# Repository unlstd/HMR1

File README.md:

> This repo documents my progress in creating my first fully functional 16-bit computer. At first, it wasn't even supposed to be public. I made it public mainly to make it easier to work on the project across different devices and to get quicker help from my friends. Because of that, please consider this project more as a documentation of someone's progress rather than a fully documented architecture.

With that being said, I can now introduce you to the project and what I'm trying to achieve.

HMR1 is a 16-bit, non-pipelined computer running at 4 MHz with 8 GPRs.

It contains the following components:

* ALU with two 16-bit special registers for latching operands
* MAR
* MDR
* SP
* HP
* IR
* 8 × 16-bit GPRs
* FR
* PC (also known as IP)
* Internal 4 MHz clock and reset signal generator
* CU
* IC (Interrupt Controller)

The computer itself is still a work in progress, but most of it is already done.

You can track the progress using the checklist below:

* [x] ALU
* [x] MAR
* [x] MDR
* [x] SP
* [x] HP
* [x] GPRs
* [x] FR
* [x] PC
* [x] IR
* [x] IC
* [x] CU
* [x] Motherboard
* [x] Internal 4 MHz clock and reset signal generator

So, even though all the schematics are complete, that doesn't mean the PCBs have been made yet. Here's a little checklist to track the progress of designing the actual PCBs:

* [ ] ALU
* [ ] MAR
* [x] MDR
* [x] SP
* [x] HP
* [x] GPRs
* [ ] FR
* [x] PC
* [ ] IR
* [ ] IC
* [ ] CU
* [ ] Motherboard
* [ ] Internal 4 MHz clock and reset signal generator

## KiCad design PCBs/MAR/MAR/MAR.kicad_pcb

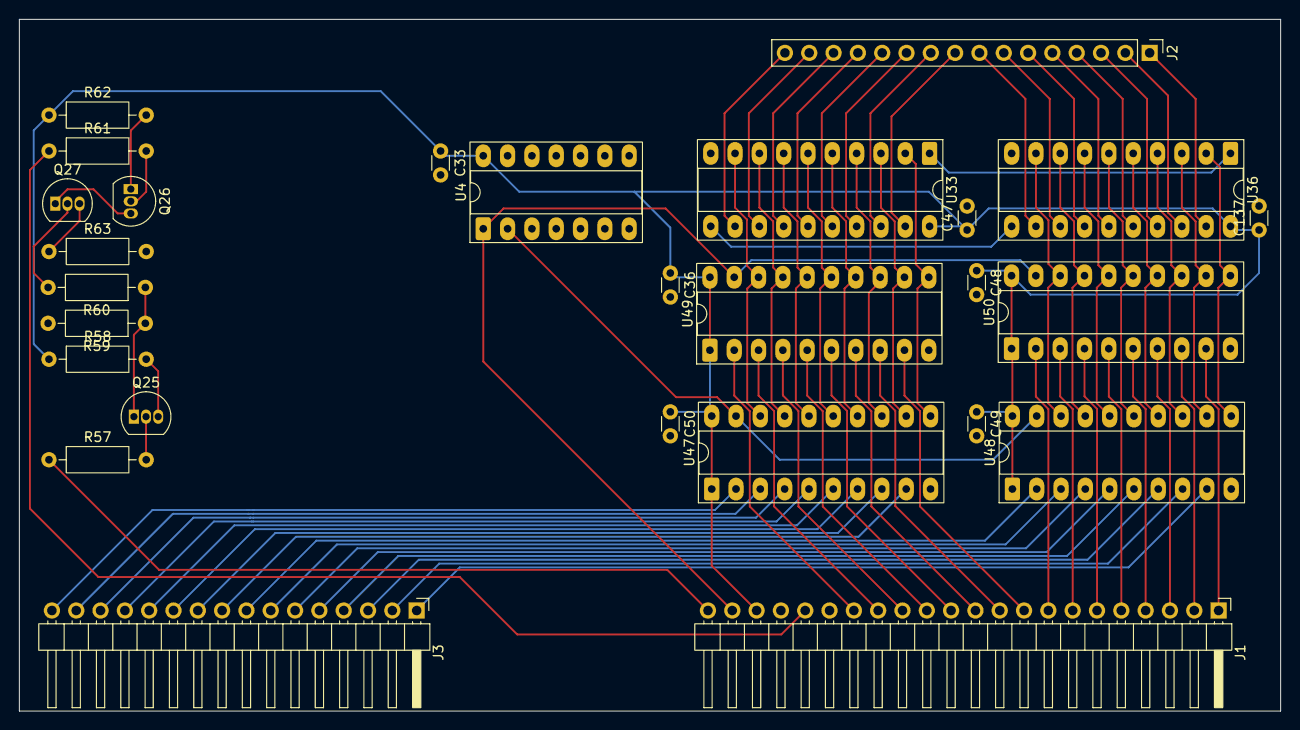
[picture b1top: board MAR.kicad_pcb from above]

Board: 2 copper layers, 131.8 x 72.2 mm, 27 parts (0 on the bottom side), 80 nets.

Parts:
C33, C36, C47, C48, C49, C50, C137: 100nF; C_Disc_D3.0mm_W1.6mm_P2.50mm
J1: MAR_DATA; PinHeader_1x22_P2.54mm_Horizontal
J2: MAR_MC; PinHeader_1x16_P2.54mm_Vertical
J3: MAR_ADDR; PinHeader_1x16_P2.54mm_Horizontal
Q25: BC557; TO-92_Inline
Q26, Q27: BC547; TO-92_Inline
R57, R58, R59, R60, R61, R62, R63: 10k; R_Axial_DIN0207_L6.3mm_D2.5mm_P10.16mm_Horizontal
U4: 74HC04; DIP-14_W7.62mm_Socket_LongPads
U33, U36: 74HC574_w_Pwr; DIP-20_W7.62mm_Socket_LongPads
U47, U48, U49, U50: 74HC245; DIP-20_W7.62mm_Socket_LongPads

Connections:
/A0: J3.1, U48.9 (A7)
/A1: J3.2, U48.8 (A6)
/A2: J3.3, U48.7 (A5)
/A3: J3.4, U48.6 (A4)
/A4: J3.5, U48.5 (A3)
/A5: J3.6, U48.4 (A2)
/A6: J3.7, U48.3 (A1)
/A7: J3.8, U48.2 (A0)
/A8: J3.9, U47.9 (A7)
/A9: J3.10, U47.8 (A6)
/A10: J3.11, U47.7 (A5)
/A11: J3.12, U47.6 (A4)
/A12: J3.13, U47.5 (A3)
/A13: J3.14, U47.4 (A2)
/A14: J3.15, U47.3 (A1)
/A15: J3.16, U47.2 (A0)
/CLK: J1.18, R61.1
/D0: J1.1, U50.9 (A7)
/D1: J1.2, U50.8 (A6)
/D2: J1.3, U50.7 (A5)
/D3: J1.4, U50.6 (A4)
/D4: J1.5, U50.5 (A3)
/D5: J1.6, U50.4 (A2)
/D6: J1.7, U50.3 (A1)
/D7: J1.8, U50.2 (A0)
/D8: J1.9, U49.9 (A7)
/D9: J1.10, U49.8 (A6)
/D10: J1.11, U49.7 (A5)
/D11: J1.12, U49.6 (A4)
/D12: J1.13, U49.5 (A3)
/D13: J1.14, U49.4 (A2)
/D14: J1.15, U49.3 (A1)
/D15: J1.16, U49.2 (A0)
/M0: J2.1, U36.19 (Q0)
/M1: J2.2, U36.18 (Q1)
/M2: J2.3, U36.17 (Q2)
/M3: J2.4, U36.16 (Q3)
/M4: J2.5, U36.15 (Q4)
/M5: J2.6, U36.14 (Q5)
/M6: J2.7, U36.13 (Q6)
/M7: J2.8, U36.12 (Q7)
/M8: J2.9, U33.19 (Q0)
/M9: J2.10, U33.18 (Q1)
/M10: J2.11, U33.17 (Q2)
/M11: J2.12, U33.16 (Q3)
/M12: J2.13, U33.15 (Q4)
/M13: J2.14, U33.14 (Q5)
/M14: J2.15, U33.13 (Q6)
/M15: J2.16, U33.12 (Q7)
/MAR_GATE[0->DATA;1->ADDR]: J1.21, U4.1, U49.19 (CE), U50.19 (CE)
/MAR_IN#: J1.22, R57.1
/Vcc: C33.1, C36.1, C47.1, C48.1, C49.1, C50.1, C137.1, J1.20, R58.1, R62.1, U4.14 (VCC), U33.20 (Vcc), U36.20 (Vcc), U47.1 (A->B), U47.20 (VCC), U48.1 (A->B), U48.20 (VCC), U49.1 (A->B), U49.20 (VCC), U50.1 (A->B), U50.20 (VCC)
GND: C33.2, C36.2, C47.2, C48.2, C49.2, C50.2, C137.2, J1.19, R59.2, R63.2, U4.7 (GND), U33.10 (GND), U36.10 (GND), U47.10 (GND), U48.10 (GND), U49.10 (GND), U50.10 (GND)
unnamed: U33.11 (CP), U36.11 (CP)
unnamed: Q27.3 (E), R63.1
unnamed: U33.1 (~OE), U36.1 (~OE)
unnamed: Q25.2 (B), R57.2
unnamed: Q25.1 (C), R59.1, R60.1
unnamed: Q25.3 (E), R58.2
unnamed: Q26.2 (B), R61.2
unnamed: Q26.1 (C), R62.2
unnamed: Q26.3 (E), Q27.1 (C)
unnamed: Q27.2 (B), R60.2
unnamed: U33.2 (D0), U47.11 (B7), U49.11 (B7)
unnamed: U33.3 (D1), U47.12 (B6), U49.12 (B6)
unnamed: U33.4 (D2), U47.13 (B5), U49.13 (B5)
unnamed: U33.5 (D3), U47.14 (B4), U49.14 (B4)
unnamed: U33.6 (D4), U47.15 (B3), U49.15 (B3)
unnamed: U33.7 (D5), U47.16 (B2), U49.16 (B2)
unnamed: U33.8 (D6), U47.17 (B1), U49.17 (B1)
unnamed: U33.9 (D7), U47.18 (B0), U49.18 (B0)
unnamed: U36.2 (D0), U48.11 (B7), U50.11 (B7)
unnamed: U36.3 (D1), U48.12 (B6), U50.12 (B6)
unnamed: U36.4 (D2), U48.13 (B5), U50.13 (B5)
unnamed: U36.5 (D3), U48.14 (B4), U50.14 (B4)
unnamed: U36.6 (D4), U48.15 (B3), U50.15 (B3)
unnamed: U36.7 (D5), U48.16 (B2), U50.16 (B2)
unnamed: U36.8 (D6), U48.17 (B1), U50.17 (B1)
unnamed: U36.9 (D7), U48.18 (B0), U50.18 (B0)
unnamed: U4.2, U47.19 (CE), U48.19 (CE)

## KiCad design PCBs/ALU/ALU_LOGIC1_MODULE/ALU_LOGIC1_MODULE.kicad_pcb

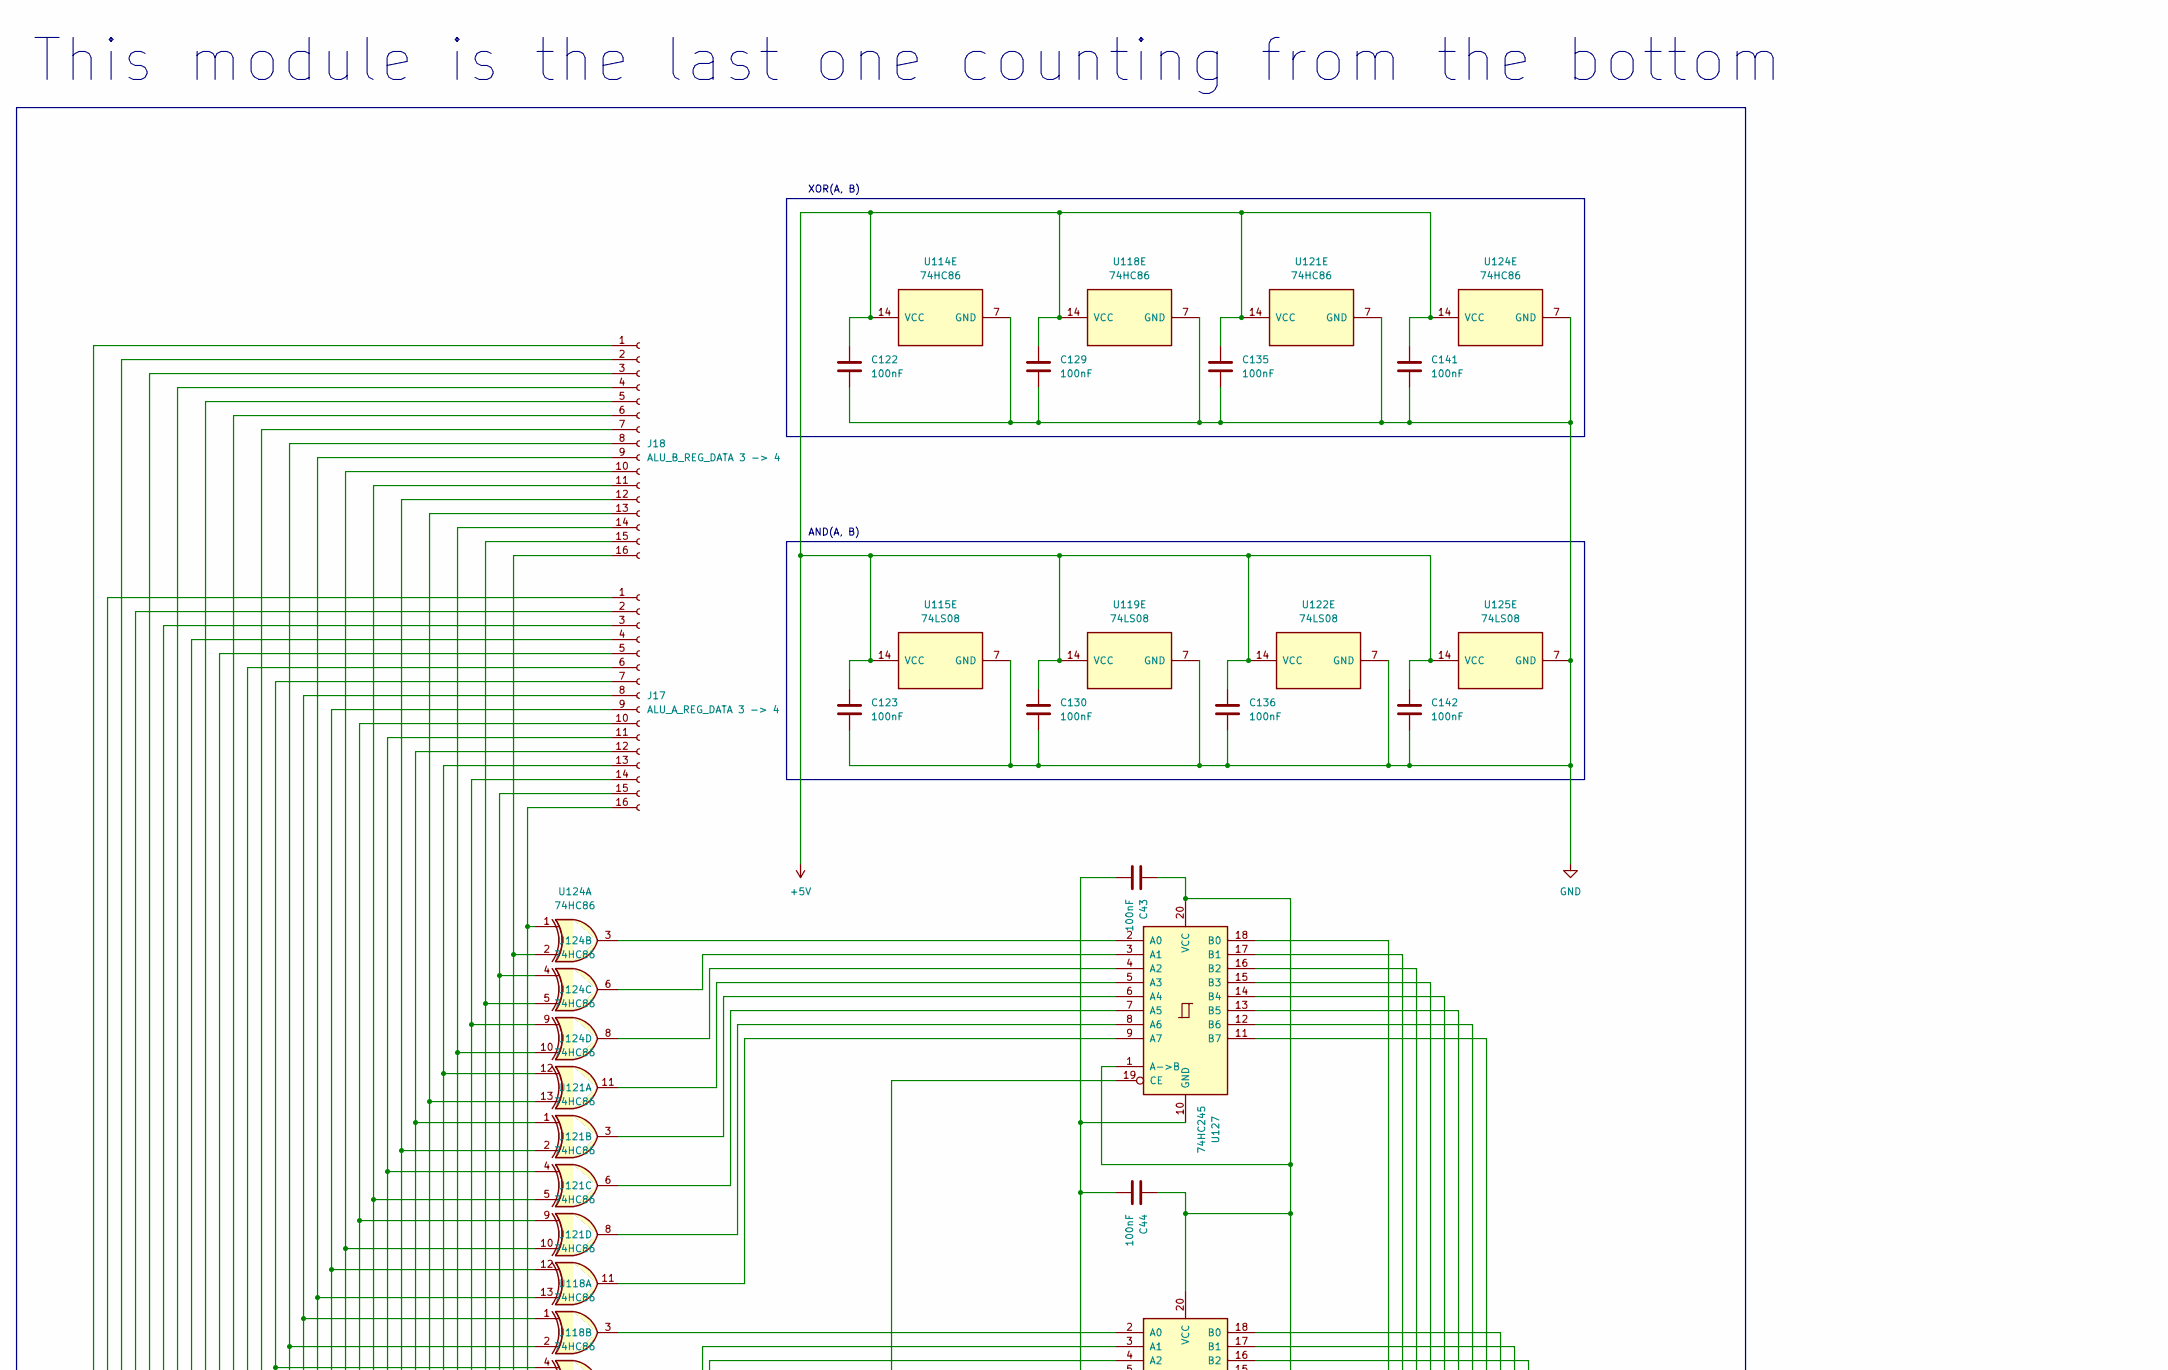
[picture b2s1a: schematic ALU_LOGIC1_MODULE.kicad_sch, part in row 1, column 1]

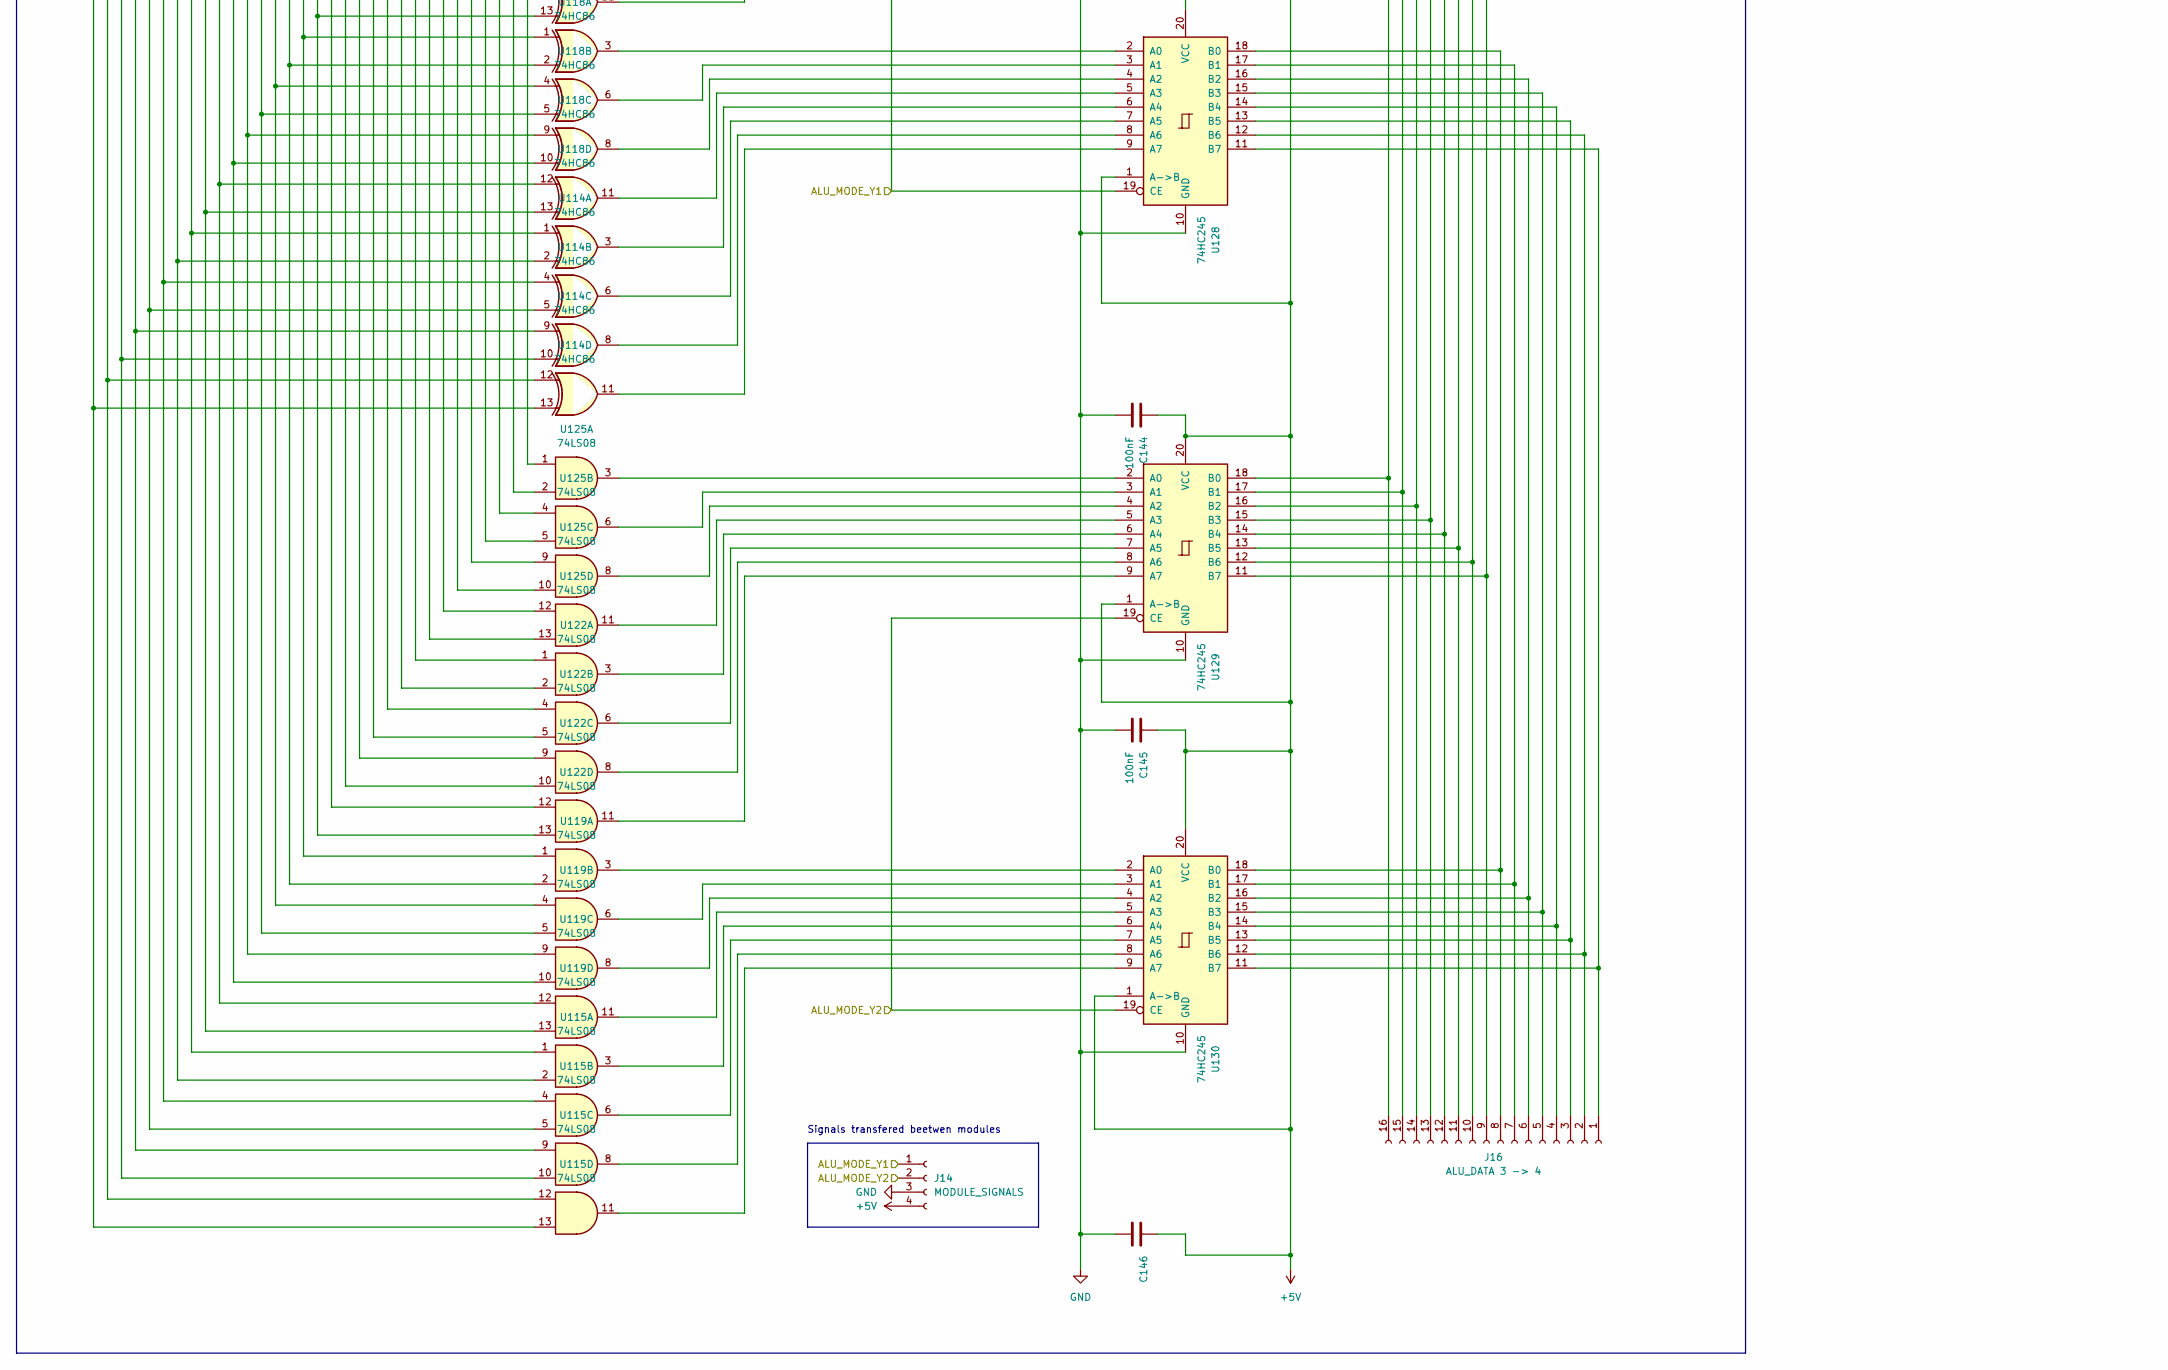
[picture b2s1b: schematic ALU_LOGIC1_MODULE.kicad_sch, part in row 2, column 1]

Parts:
C43, C44, C122, C123, C129, C130, C135, C136, C141, C142, C144, C145, C146: 100nF; C_Disc_D3.0mm_W1.6mm_P2.50mm
J14: MODULE_SIGNALS; PinSocket_1x04_P2.54mm_Vertical
J16: ALU_DATA 3 -> 4; PinSocket_1x16_P2.54mm_Vertical
J17: ALU_A_REG_DATA 3 -> 4; PinSocket_1x16_P2.54mm_Vertical
J18: ALU_B_REG_DATA 3 -> 4; PinSocket_1x16_P2.54mm_Vertical
U114, U118, U121, U124: 74HC86; DIP-14_W7.62mm_Socket_LongPads
U115, U119, U122, U125: 74LS08; DIP-14_W7.62mm_Socket_LongPads
U127, U128, U129, U130: 74HC245; DIP-20_W7.62mm_Socket_LongPads

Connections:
+5V: C43.1, C44.1, C122.1, C123.1, C129.1, C130.1, C135.1, C136.1, C141.1, C142.1, C144.1, C145.1, C146.1, J14.4, U114.14 (VCC), U115.14 (VCC), U118.14 (VCC), U119.14 (VCC), U121.14 (VCC), U122.14 (VCC), U124.14 (VCC), U125.14 (VCC), U127.1 (A->B), U127.20 (VCC), U128.1 (A->B), U128.20 (VCC), U129.1 (A->B), U129.20 (VCC), U130.1 (A->B), U130.20 (VCC)
/ALU_MODE_Y1: J14.1, U127.19 (CE), U128.19 (CE)
/ALU_MODE_Y2: J14.2, U129.19 (CE), U130.19 (CE)
GND: C43.2, C44.2, C122.2, C123.2, C129.2, C130.2, C135.2, C136.2, C141.2, C142.2, C144.2, C145.2, C146.2, J14.3, U114.7 (GND), U115.7 (GND), U118.7 (GND), U119.7 (GND), U121.7 (GND), U122.7 (GND), U124.7 (GND), U125.7 (GND), U127.10 (GND), U128.10 (GND), U129.10 (GND), U130.10 (GND)
unnamed: J16.1, U128.11 (B7), U130.11 (B7)
unnamed: J16.2, U128.12 (B6), U130.12 (B6)
unnamed: J16.3, U128.13 (B5), U130.13 (B5)
unnamed: J16.4, U128.14 (B4), U130.14 (B4)
unnamed: J16.5, U128.15 (B3), U130.15 (B3)
unnamed: J16.6, U128.16 (B2), U130.16 (B2)
unnamed: J16.7, U128.17 (B1), U130.17 (B1)
unnamed: J16.8, U128.18 (B0), U130.18 (B0)
unnamed: J16.9, U127.11 (B7), U129.11 (B7)
unnamed: J16.10, U127.12 (B6), U129.12 (B6)
unnamed: J16.11, U127.13 (B5), U129.13 (B5)
unnamed: J16.12, U127.14 (B4), U129.14 (B4)
unnamed: J16.13, U127.15 (B3), U129.15 (B3)
unnamed: J16.14, U127.16 (B2), U129.16 (B2)
unnamed: J16.15, U127.17 (B1), U129.17 (B1)
unnamed: J16.16, U127.18 (B0), U129.18 (B0)
unnamed: J17.1, U114.12, U115.12
unnamed: J17.2, U114.9, U115.9
unnamed: J17.3, U114.4, U115.4
unnamed: J17.4, U114.1, U115.1
unnamed: J17.5, U118.12, U119.12
unnamed: J17.6, U118.9, U119.9
unnamed: J17.7, U118.4, U119.4
unnamed: J17.8, U118.1, U119.1
unnamed: J17.9, U121.12, U122.12
unnamed: J17.10, U121.9, U122.9
unnamed: J17.11, U121.4, U122.4
unnamed: J17.12, U121.1, U122.1
unnamed: J17.13, U124.12, U125.12
unnamed: J17.14, U124.9, U125.9
unnamed: J17.15, U124.4, U125.4
unnamed: J17.16, U124.1, U125.1
unnamed: J18.1, U114.13, U115.13
unnamed: J18.2, U114.10, U115.10
unnamed: J18.3, U114.5, U115.5
unnamed: J18.4, U114.2, U115.2
unnamed: J18.5, U118.13, U119.13
unnamed: J18.6, U118.10, U119.10
unnamed: J18.7, U118.5, U119.5
unnamed: J18.8, U118.2, U119.2
unnamed: J18.9, U121.13, U122.13
unnamed: J18.10, U121.10, U122.10
unnamed: J18.11, U121.5, U122.5
unnamed: J18.12, U121.2, U122.2
unnamed: J18.13, U124.13, U125.13
unnamed: J18.14, U124.10, U125.10
unnamed: J18.15, U124.5, U125.5
unnamed: J18.16, U124.2, U125.2
unnamed: U124.3, U127.2 (A0)
unnamed: U124.6, U127.3 (A1)
unnamed: U124.8, U127.4 (A2)
unnamed: U124.11, U127.5 (A3)
unnamed: U121.3, U127.6 (A4)
unnamed: U121.6, U127.7 (A5)
unnamed: U121.8, U127.8 (A6)
unnamed: U121.11, U127.9 (A7)
unnamed: U118.3, U128.2 (A0)
unnamed: U118.6, U128.3 (A1)
unnamed: U118.8, U128.4 (A2)
unnamed: U118.11, U128.5 (A3)
unnamed: U114.3, U128.6 (A4)
unnamed: U114.6, U128.7 (A5)
unnamed: U114.8, U128.8 (A6)
unnamed: U114.11, U128.9 (A7)
unnamed: U125.3, U129.2 (A0)
unnamed: U125.6, U129.3 (A1)
unnamed: U125.8, U129.4 (A2)
unnamed: U125.11, U129.5 (A3)
unnamed: U122.3, U129.6 (A4)
unnamed: U122.6, U129.7 (A5)
unnamed: U122.8, U129.8 (A6)
unnamed: U122.11, U129.9 (A7)
unnamed: U119.3, U130.2 (A0)
unnamed: U119.6, U130.3 (A1)
unnamed: U119.8, U130.4 (A2)
unnamed: U119.11, U130.5 (A3)
unnamed: U115.3, U130.6 (A4)
unnamed: U115.6, U130.7 (A5)
unnamed: U115.8, U130.8 (A6)
unnamed: U115.11, U130.9 (A7)

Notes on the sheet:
Signals transfered beetwen modules
XOR(A, B)
AND(A, B)
This module is the last one counting from the bottom

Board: 2 copper layers, 29 parts (0 on the bottom side), 84 nets, no tracks yet.

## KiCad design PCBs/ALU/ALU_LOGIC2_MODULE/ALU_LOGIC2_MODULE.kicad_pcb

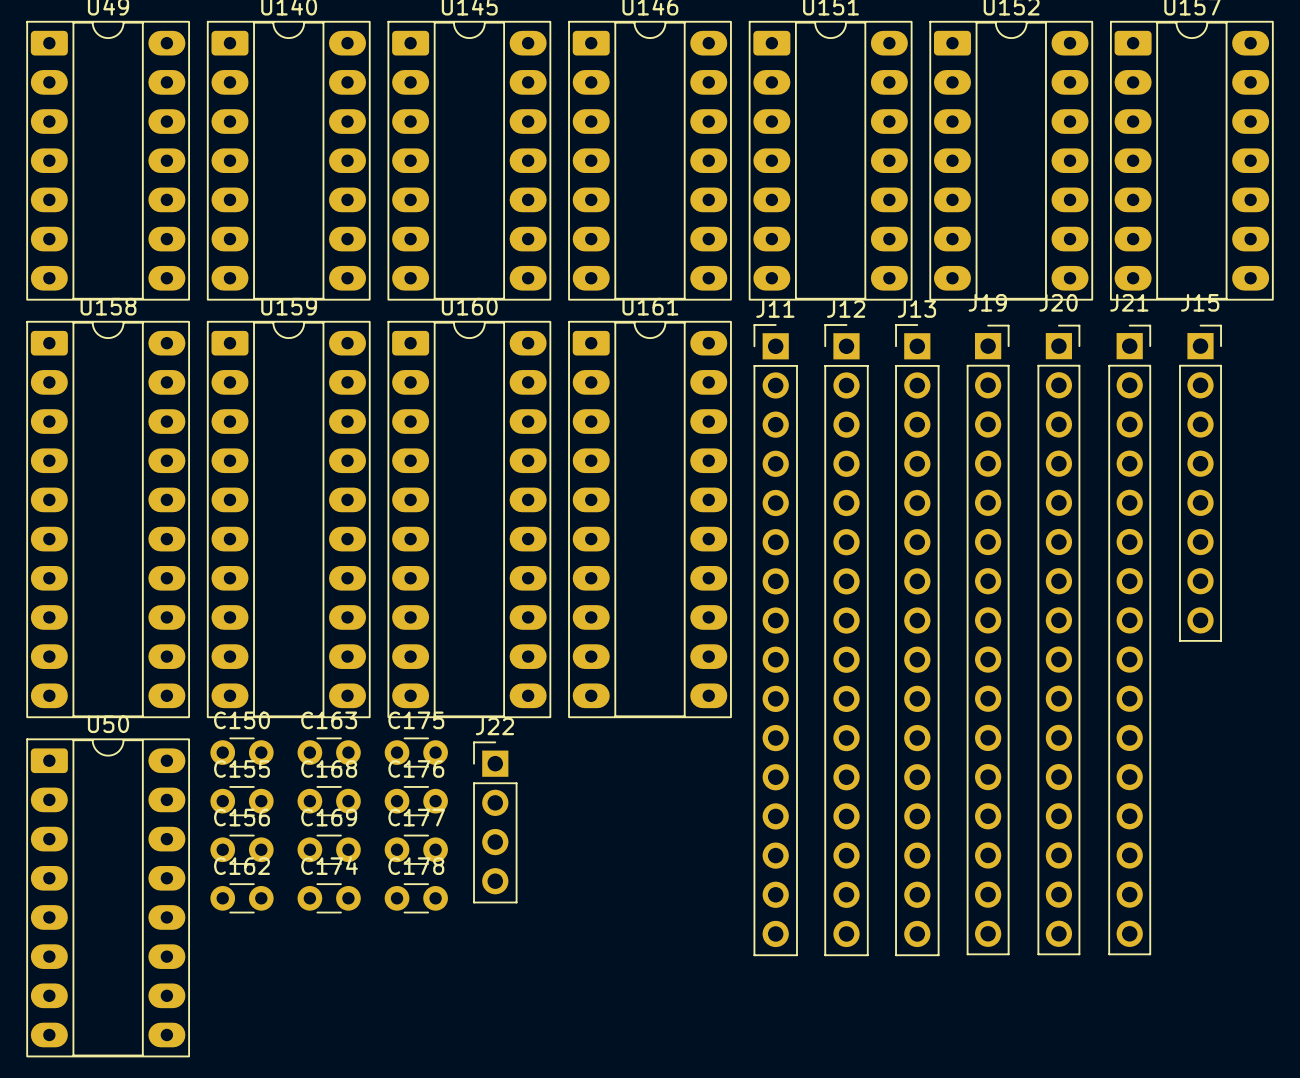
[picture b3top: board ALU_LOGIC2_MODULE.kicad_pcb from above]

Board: 2 copper layers, 32 parts (0 on the bottom side), 92 nets, no tracks yet.

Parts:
C150, C155, C156, C162, C163, C168, C169, C174, C175, C176, C177, C178: 100nF; C_Disc_D3.0mm_W1.6mm_P2.50mm
J11: Conn_01x16_Pin 3 -> 4; PinHeader_1x16_P2.54mm_Vertical
J12: ALU_A_REG_DATA 3 -> 4; PinHeader_1x16_P2.54mm_Vertical
J13: ALU_B_REG_DATA 3 -> 4; PinHeader_1x16_P2.54mm_Vertical
J15: MODULE_SIGNALS; PinSocket_1x08_P2.54mm_Vertical
J19: ALU_B_REG_DATA 2 -> 3; PinSocket_1x16_P2.54mm_Vertical
J20: ALU_DATA 2 -> 3; PinSocket_1x16_P2.54mm_Vertical
J21: ALU_A_REG_DATA 2 -> 3; PinSocket_1x16_P2.54mm_Vertical
J22: MODULE_SIGNALS; PinHeader_1x04_P2.54mm_Vertical
U49, U146, U152: 74HC04; DIP-14_W7.62mm_Socket_LongPads
U50: 74HC138; DIP-16_W7.62mm_Socket_LongPads
U140, U145, U151, U157: 74LS32; DIP-14_W7.62mm_Socket_LongPads
U158, U159, U160, U161: 74HC245; DIP-20_W7.62mm_Socket_LongPads

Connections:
+5V: C150.1, C155.1, C156.1, C162.1, C163.1, C168.1, C169.1, C174.1, C175.1, C176.1, C177.1, C178.1, J15.8, J22.4, U49.14 (VCC), U50.6 (E2), U50.16 (VCC), U140.14 (VCC), U145.14 (VCC), U146.14 (VCC), U151.14 (VCC), U152.14 (VCC), U157.14 (VCC), U158.1 (A->B), U158.20 (VCC), U159.1 (A->B), U159.20 (VCC), U160.1 (A->B), U160.20 (VCC), U161.1 (A->B), U161.20 (VCC)
/ALU_MODE0: J15.4, U50.1 (A0)
/ALU_MODE1: J15.5, U50.2 (A1)
/ALU_MODE2: J15.6, U50.3 (A2)
/ALU_MODE_Y0: J15.1, U50.15 (~Y0)
/ALU_MODE_Y1: J22.1, U50.14 (~Y1)
/ALU_MODE_Y2: J22.2, U50.13 (~Y2)
/ALU_MODE_Y5: J15.2, U50.10 (~Y5)
/ALU_MODE_Y6: J15.3, U50.9 (~Y6)
GND: C150.2, C155.2, C156.2, C162.2, C163.2, C168.2, C169.2, C174.2, C175.2, C176.2, C177.2, C178.2, J15.7, J22.3, U49.7 (GND), U50.4 (~E0), U50.5 (~E1), U50.8 (GND), U140.7 (GND), U145.7 (GND), U146.7 (GND), U151.7 (GND), U152.7 (GND), U157.7 (GND), U158.10 (GND), U159.10 (GND), U160.10 (GND), U161.10 (GND)
unnamed: J11.1, J20.1, U159.11 (B7), U161.11 (B7)
unnamed: J11.2, J20.2, U159.12 (B6), U161.12 (B6)
unnamed: J11.3, J20.3, U159.13 (B5), U161.13 (B5)
unnamed: J11.4, J20.4, U159.14 (B4), U161.14 (B4)
unnamed: J11.5, J20.5, U159.15 (B3), U161.15 (B3)
unnamed: J11.6, J20.6, U159.16 (B2), U161.16 (B2)
unnamed: J11.7, J20.7, U159.17 (B1), U161.17 (B1)
unnamed: J11.8, J20.8, U159.18 (B0), U161.18 (B0)
unnamed: J11.9, J20.9, U158.11 (B7), U160.11 (B7)
unnamed: J11.10, J20.10, U158.12 (B6), U160.12 (B6)
unnamed: J11.11, J20.11, U158.13 (B5), U160.13 (B5)
unnamed: J11.12, J20.12, U158.14 (B4), U160.14 (B4)
unnamed: J11.13, J20.13, U158.15 (B3), U160.15 (B3)
unnamed: J11.14, J20.14, U158.16 (B2), U160.16 (B2)
unnamed: J11.15, J20.15, U158.17 (B1), U160.17 (B1)
unnamed: J11.16, J20.16, U158.18 (B0), U160.18 (B0)
unnamed: J12.1, J21.1, U49.9, U140.12
unnamed: J12.2, J21.2, U49.5, U140.9
unnamed: J12.3, J21.3, U49.3, U140.4
unnamed: J12.4, J21.4, U49.1, U140.1
unnamed: J12.5, J21.5, U145.12, U146.13
unnamed: J12.6, J21.6, U145.9, U146.11
unnamed: J12.7, J21.7, U145.4, U146.9
unnamed: J12.8, J21.8, U145.1, U146.5
unnamed: J12.9, J21.9, U146.3, U151.12
unnamed: J12.10, J21.10, U146.1, U151.9
unnamed: J12.11, J21.11, U151.4, U152.13
unnamed: J12.12, J21.12, U151.1, U152.11
unnamed: J12.13, J21.13, U152.9, U157.12
unnamed: J12.14, J21.14, U152.5, U157.9
unnamed: J12.15, J21.15, U152.3, U157.4
unnamed: J12.16, J21.16, U152.1, U157.1
unnamed: J13.1, J19.1, U157.2
unnamed: J13.2, J19.2, U157.5
unnamed: J13.3, J19.3, U157.10
unnamed: J13.4, J19.4, U157.13
unnamed: J13.5, J19.5, U151.2
unnamed: J13.6, J19.6, U151.5
unnamed: J13.7, J19.7, U151.10
unnamed: J13.8, J19.8, U151.13
unnamed: J13.9, J19.9, U145.2
unnamed: J13.10, J19.10, U145.5
unnamed: J13.11, J19.11, U145.10
unnamed: J13.12, J19.12, U145.13
unnamed: J13.13, J19.13, U140.2
unnamed: J13.14, J19.14, U140.5
unnamed: J13.15, J19.15, U140.10
unnamed: J13.16, J19.16, U140.13
unnamed: U157.3, U158.2 (A0)
unnamed: U157.6, U158.3 (A1)
unnamed: U157.8, U158.4 (A2)
unnamed: U157.11, U158.5 (A3)
unnamed: U151.3, U158.6 (A4)
unnamed: U151.6, U158.7 (A5)
unnamed: U151.8, U158.8 (A6)
unnamed: U151.11, U158.9 (A7)
unnamed: U50.12 (~Y3), U158.19 (CE), U159.19 (CE)
unnamed: U145.3, U159.2 (A0)
unnamed: U145.6, U159.3 (A1)
unnamed: U145.8, U159.4 (A2)
unnamed: U145.11, U159.5 (A3)
unnamed: U140.3, U159.6 (A4)
unnamed: U140.6, U159.7 (A5)
unnamed: U140.8, U159.8 (A6)
unnamed: U140.11, U159.9 (A7)
unnamed: U152.2, U160.2 (A0)
unnamed: U152.4, U160.3 (A1)
unnamed: U152.6, U160.4 (A2)
unnamed: U152.8, U160.5 (A3)
unnamed: U152.10, U160.6 (A4)
unnamed: U152.12, U160.7 (A5)
unnamed: U146.2, U160.8 (A6)
unnamed: U146.4, U160.9 (A7)
unnamed: U50.11 (~Y4), U160.19 (CE), U161.19 (CE)
unnamed: U146.6, U161.2 (A0)
unnamed: U146.8, U161.3 (A1)
unnamed: U146.10, U161.4 (A2)
unnamed: U146.12, U161.5 (A3)
unnamed: U49.2, U161.6 (A4)
unnamed: U49.4, U161.7 (A5)
unnamed: U49.6, U161.8 (A6)
unnamed: U49.8, U161.9 (A7)

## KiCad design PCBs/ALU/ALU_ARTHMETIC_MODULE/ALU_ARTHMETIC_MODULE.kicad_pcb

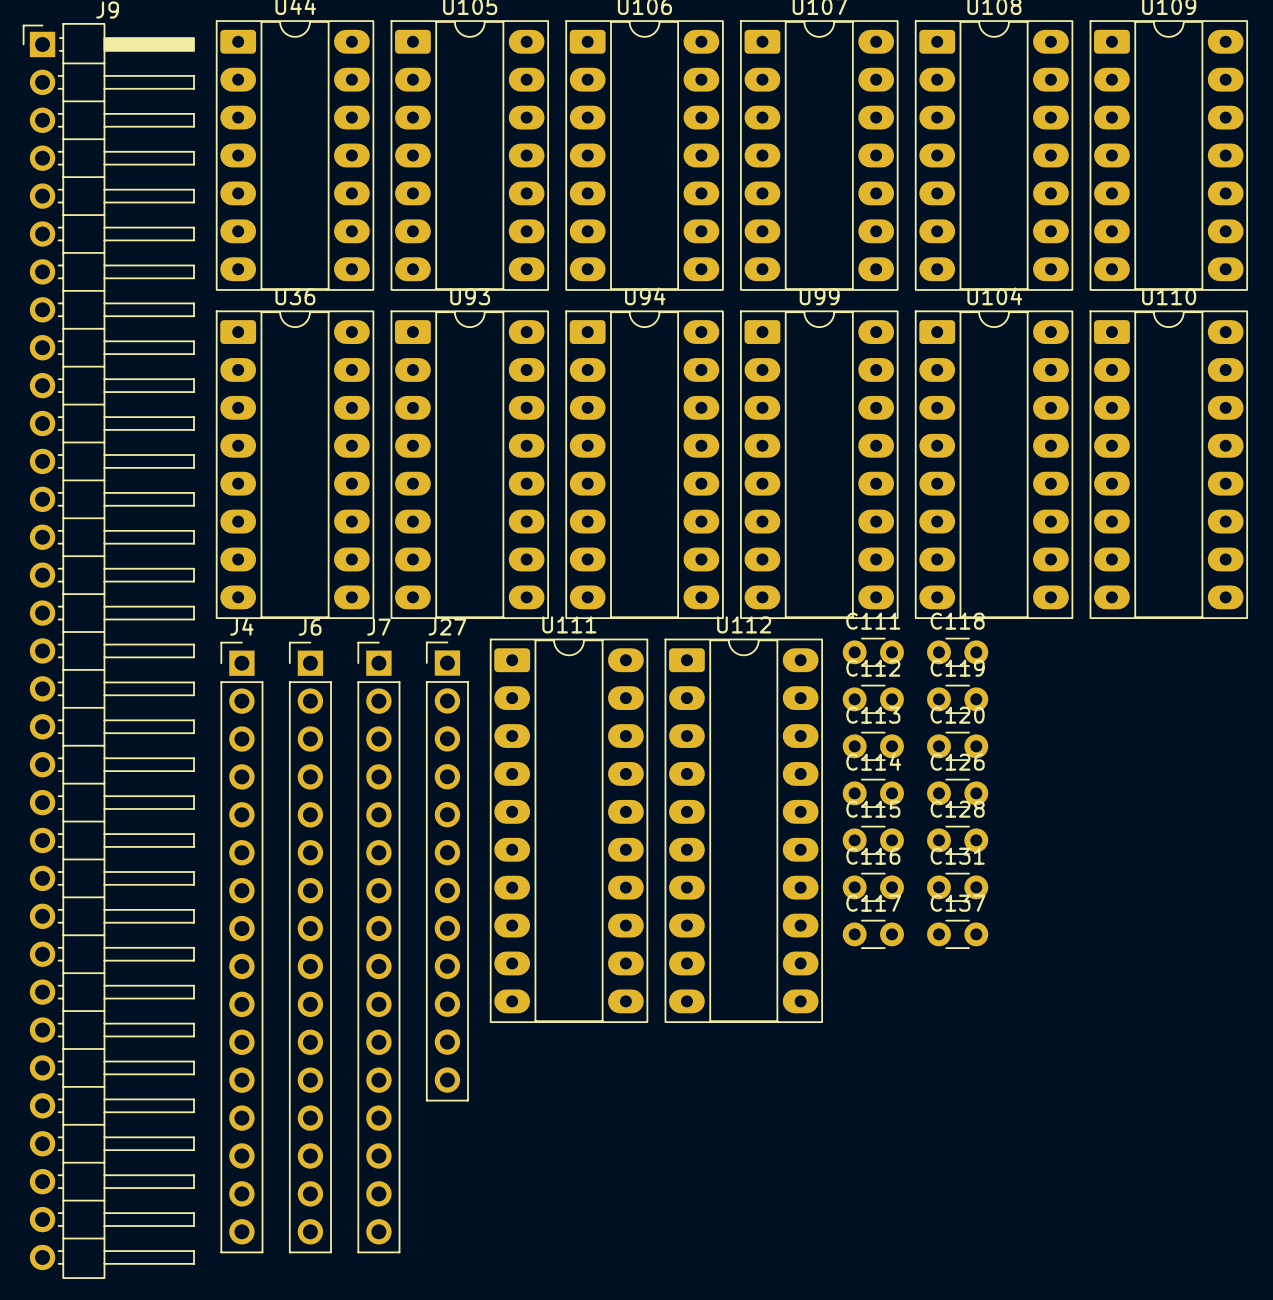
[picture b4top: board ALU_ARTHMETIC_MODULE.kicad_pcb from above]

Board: 2 copper layers, 33 parts (0 on the bottom side), 106 nets, no tracks yet.

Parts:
C111, C112, C113, C114, C115, C116, C117, C118, C119, C120, C126, C128, C131, C137: 100nF; C_Disc_D3.0mm_W1.6mm_P2.50mm
J4: ALU_A_REG_DATA 1 -> 2; PinHeader_1x16_P2.54mm_Vertical
J6: ALU_B_REG_DATA 1 -> 2; PinHeader_1x16_P2.54mm_Vertical
J7: ALU_DATA_BUS 1 -> 2; PinHeader_1x16_P2.54mm_Vertical
J9: ALU_DATA; PinHeader_1x33_P2.54mm_Horizontal
J27: MODULE_SIGNALS; PinHeader_1x12_P2.54mm_Vertical
U36: 74LS153; DIP-16_W7.62mm_Socket_LongPads
U44: 74HC86; DIP-14_W7.62mm_Socket_LongPads
U93, U94, U99, U104: 74LS283; DIP-16_W7.62mm_Socket_LongPads
U105, U106, U107, U108: 74LS32; DIP-14_W7.62mm_Socket_LongPads
U109: 74LS08; DIP-14_W7.62mm_Socket_LongPads
U110: 74LS157; DIP-16_W7.62mm_Socket_LongPads
U111, U112: 74HC245; DIP-20_W7.62mm_Socket_LongPads

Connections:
+5V: C111.1, C112.1, C113.1, C114.1, C115.1, C116.1, C117.1, C118.1, C119.1, C120.1, C126.1, C128.1, C131.1, C137.1, J27.12, U36.5 (I1a), U36.15 (Eb), U36.16 (VCC), U44.10, U44.12, U44.14 (VCC), U93.16 (VCC), U94.16 (VCC), U99.16 (VCC), U104.16 (VCC), U105.14 (VCC), U106.14 (VCC), U107.14 (VCC), U108.14 (VCC), U109.14 (VCC), U110.16 (VCC), U111.1 (A->B), U111.20 (VCC), U112.1 (A->B), U112.20 (VCC)
/#ALU_A_IN: J9.8, J27.8
/#ALU_B_IN: J9.7, J27.7
/A15_BIT: J27.5, U44.2, U44.5
/ALU_CARRY_SEL0: J9.5, U36.14 (S0)
/ALU_CARRY_SEL1: J9.4, U36.2 (S1)
/ALU_FR_CARRY: J9.12, U104.9 (C4)
/ALU_FR_OV: J9.9, U110.4 (Za)
/ALU_FR_SIGN: J9.10, U44.1, U104.10 (S4), U108.12, U112.9 (A7)
/ALU_FR_ZERO: J9.11, U44.8
/ALU_INV_B: J9.6, J27.9, U110.1 (S)
/ALU_MODE0: J9.3, J27.2
/ALU_MODE1: J9.2, J27.3
/ALU_MODE2: J9.1, J27.4
/ALU_MODE_Y0: J27.1, U111.19 (CE), U112.19 (CE)
/B15_BIT: J27.6, U44.4
/CLK: J9.31, J27.10
/D0: J7.1, J9.14, U111.18 (B0)
/D1: J7.2, J9.15, U111.17 (B1)
/D2: J7.3, J9.16, U111.16 (B2)
/D3: J7.4, J9.17, U111.15 (B3)
/D4: J7.5, J9.18, U111.14 (B4)
/D5: J7.6, J9.19, U111.13 (B5)
/D6: J7.7, J9.20, U111.12 (B6)
/D7: J7.8, J9.21, U111.11 (B7)
/D8: J7.9, J9.22, U112.18 (B0)
/D9: J7.10, J9.23, U112.17 (B1)
/D10: J7.11, J9.24, U112.16 (B2)
/D11: J7.12, J9.25, U112.15 (B3)
/D12: J7.13, J9.26, U112.14 (B4)
/D13: J7.14, J9.27, U112.13 (B5)
/D14: J7.15, J9.28, U112.12 (B6)
/D15: J7.16, J9.29, U112.11 (B7)
/FR_CARRY_IN: J9.13, U36.4 (I2a)
GND: C111.2, C112.2, C113.2, C114.2, C115.2, C116.2, C117.2, C118.2, C119.2, C120.2, C126.2, C128.2, C131.2, C137.2, J9.32, J27.11, U36.1 (Ea), U36.3 (I3a), U36.6 (I0a), U36.8 (GND), U36.10 (I0b), U36.11 (I1b), U36.12 (I2b), U36.13 (I3b), U44.7 (GND), U93.8 (GND), U94.8 (GND), U99.8 (GND), U104.8 (GND), U105.7 (GND), U106.7 (GND), U107.7 (GND), U108.7 (GND), U109.7 (GND), U110.5 (I0b), U110.6 (I1b), U110.8 (GND), U110.10 (I1c), U110.11 (I0c), U110.13 (I1d), U110.14 (I0d), U110.15 (E), U111.10 (GND), U112.10 (GND)
unnamed: J4.1, U93.5 (A1)
unnamed: J4.2, U93.3 (A2)
unnamed: J4.3, U93.14 (A3)
unnamed: J4.4, U93.12 (A4)
unnamed: J4.5, U94.5 (A1)
unnamed: J4.6, U94.3 (A2)
unnamed: J4.7, U94.14 (A3)
unnamed: J4.8, U94.12 (A4)
unnamed: J4.9, U99.5 (A1)
unnamed: J4.10, U99.3 (A2)
unnamed: J4.11, U99.14 (A3)
unnamed: J4.12, U99.12 (A4)
unnamed: J4.13, U104.5 (A1)
unnamed: J4.14, U104.3 (A2)
unnamed: J4.15, U104.14 (A3)
unnamed: J4.16, U104.12 (A4)
unnamed: J6.1, U93.6 (B1)
unnamed: J6.2, U93.2 (B2)
unnamed: J6.3, U93.15 (B3)
unnamed: J6.4, U93.11 (B4)
unnamed: J6.5, U94.6 (B1)
unnamed: J6.6, U94.2 (B2)
unnamed: J6.7, U94.15 (B3)
unnamed: J6.8, U94.11 (B4)
unnamed: J6.9, U99.6 (B1)
unnamed: J6.10, U99.2 (B2)
unnamed: J6.11, U99.15 (B3)
unnamed: J6.12, U99.11 (B4)
unnamed: J6.13, U104.6 (B1)
unnamed: J6.14, U104.2 (B2)
unnamed: J6.15, U104.15 (B3)
unnamed: J6.16, U104.11 (B4)
unnamed: U36.7 (Za), U93.7 (C0)
unnamed: U93.9 (C4), U94.7 (C0)
unnamed: U94.9 (C4), U99.7 (C0)
unnamed: U99.9 (C4), U104.7 (C0)
unnamed: U104.4 (S1), U108.10, U112.6 (A4)
unnamed: U104.1 (S2), U108.9, U112.7 (A5)
unnamed: U104.13 (S3), U108.13, U112.8 (A6)
unnamed: U105.3, U106.2
unnamed: U105.6, U106.1
unnamed: U105.8, U106.5
unnamed: U105.11, U106.4
unnamed: U106.3, U107.2
unnamed: U106.6, U107.1
unnamed: U106.8, U107.5
unnamed: U106.9, U108.6
unnamed: U106.10, U108.3
unnamed: U106.11, U107.4
unnamed: U106.12, U108.11
unnamed: U106.13, U108.8
unnamed: U107.6, U107.9
unnamed: U44.9, U107.8
unnamed: U107.3, U107.10
unnamed: U44.11, U109.9
unnamed: U44.3, U109.10, U109.12
unnamed: U44.6, U44.13, U109.13
unnamed: U109.8, U110.2 (I0a)
unnamed: U109.11, U110.3 (I1a)
unnamed: U93.4 (S1), U105.2, U111.2 (A0)
unnamed: U93.1 (S2), U105.1, U111.3 (A1)
unnamed: U93.13 (S3), U105.5, U111.4 (A2)
unnamed: U93.10 (S4), U105.4, U111.5 (A3)
unnamed: U94.4 (S1), U105.10, U111.6 (A4)
unnamed: U94.1 (S2), U105.9, U111.7 (A5)
unnamed: U94.13 (S3), U105.13, U111.8 (A6)
unnamed: U94.10 (S4), U105.12, U111.9 (A7)
unnamed: U99.4 (S1), U108.2, U112.2 (A0)
unnamed: U99.1 (S2), U108.1, U112.3 (A1)
unnamed: U99.13 (S3), U108.5, U112.4 (A2)
unnamed: U99.10 (S4), U108.4, U112.5 (A3)
